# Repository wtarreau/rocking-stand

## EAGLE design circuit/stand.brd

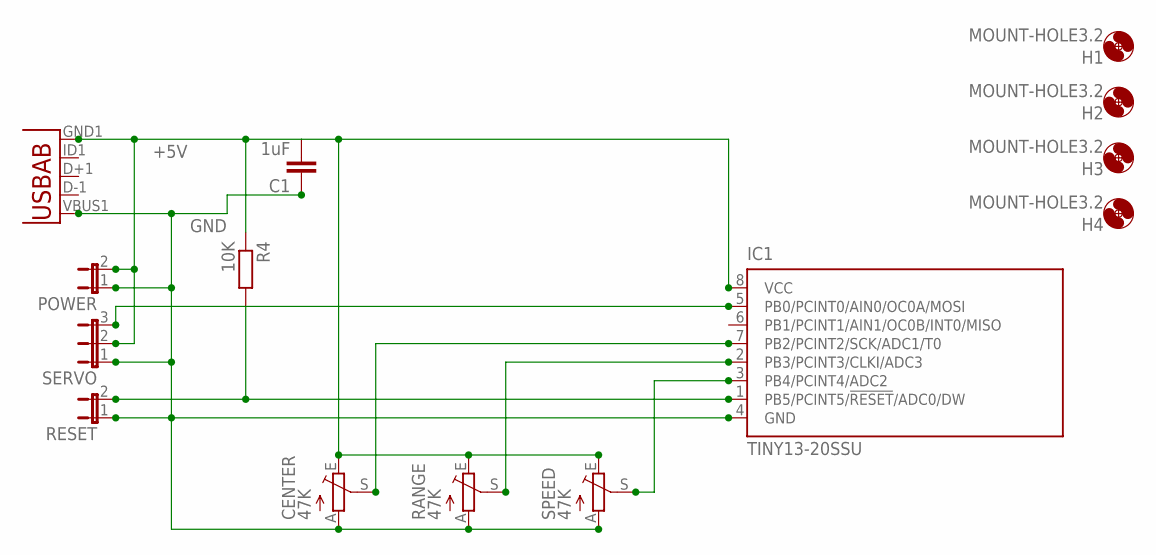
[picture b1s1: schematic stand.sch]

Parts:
C1: 1uF; C0805
CENTER: 47K; RJ6S
H1, H2, H3, H4: MOUNT-HOLE3.2; 3,2
IC1: TINY13-20SSU; 8S1
POWER: JP1E; JP1
R4: 10K; M0805
RANGE: 47K; RJ6S
RESET: JP1E; JP1
SERVO: JP2E; JP2
SPEED: 47K; RJ6S
U$1: USB""; USB-MICRO-SMD

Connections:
+5V: C1.2, CENTER.E, IC1.8 (VCC), POWER.2, R4.1, RANGE.E, SERVO.2, SPEED.E, U$1.GND1 (GND)
GND: C1.1, CENTER.A, IC1.4 (GND), POWER.1, RANGE.A, RESET.1, SERVO.1, SPEED.A, U$1.VBUS1 (VBUS)
unnamed: IC1.3 (PB4/PCINT4/ADC2), SPEED.S
unnamed: IC1.2 (PB3/PCINT3/CLKI/ADC3), RANGE.S
unnamed: IC1.1 (PB5/PCINT5/!RESET!/ADC0/DW), R4.2, RESET.2
unnamed: IC1.5 (PB0/PCINT0/AIN0/OC0A/MOSI), SERVO.3
unnamed: CENTER.S, IC1.7 (PB2/PCINT2/SCK/ADC1/T0)

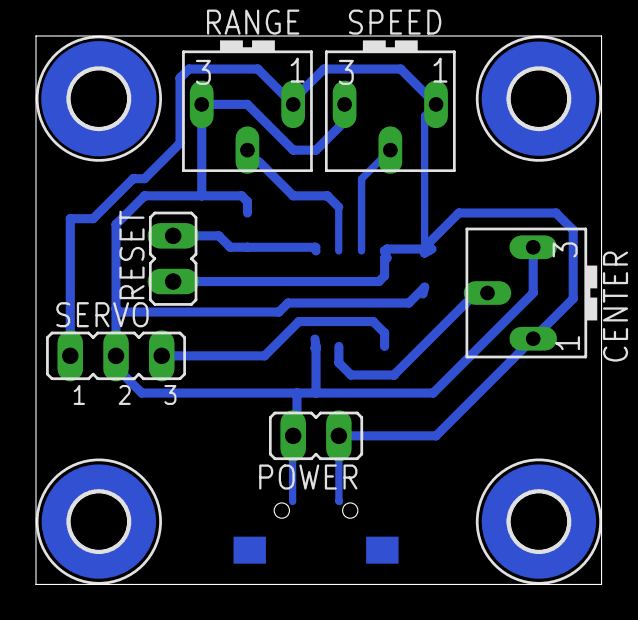
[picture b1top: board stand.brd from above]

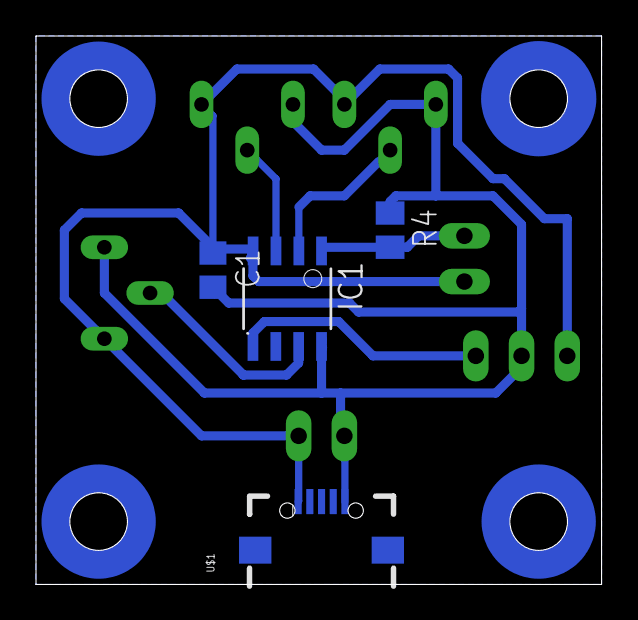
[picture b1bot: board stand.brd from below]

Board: 2 copper layers, 31.4 x 30.5 mm, 14 parts (4 on the bottom side), 7 nets.

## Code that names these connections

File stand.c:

/* stand.c - 2019/07/28 - Willy Tarreau - public domain
 *
 * This is a C AVR re-implementation of my previous rocking stand for PIC
 * that was written in 12F675 assembly. It implements a slow sine wave whose
 * amplitude, offset and frequency are controlled by 3 external potentiometers,
 * and converts it into a pulse length to drive a servo-motor. A sine wave was
 * found to be critical to avoid splashes when changing direction. The offset
 * is used to fix the center and to allow to repurpose old servos with broken
 * gears which can only operate on limited range.
 *
 * The code is written in Arduino style using setup() and loop() so that it is
 * easily ported to other environments. But it has no external dependency. It's
 * about 492 bytes on ATtiny13 and 506 on ATtiny85.
 */

/* Internal frequency, 9.6 MHz for Tiny13A, 8.0 MHz for 25/45/85 */
#ifndef F_CPU
#error "Must set F_CPU to the CPU's frequency in Hz"
#endif

#include <avr/io.h>
#include <stdint.h>

/* current angle in the highest 8 bits */
uint16_t angle = 0;

/* returns ((x*x) >> 7) + 128 using exclusively a 8*8=>16 bit signed
 * multiply. AVR: ~0x18 bytes + call to mulhi3().
 */
uint8_t sq8(int8_t x)
{
	x += 128;
	x = ((int16_t)x * x) >> 7;
	return ~x;
}

/* returns sin(angle*pi/128)*128, which is a sine centered around 0.
 * It works by approximating two paraboles. sin(x) follows x^2 and
 * 1-(x^2) very closely (6% error max) so these are sufficient.
 */
int8_t sin8(uint8_t angle)
{
	uint8_t ret = sq8(angle << 1);

	if (angle & 128)
		ret = ~ret;
	return ret + 128;
}

/* Convert microseconds to loops around an empty asm statement. Each loop was
 * measured to take 5 cycles on gcc 5.4 (vs 4 on 4.3)! This is limited to 64k
 * loops, or ~20ms at 8 MHz, 17ms at 9.6 MHz.
 */
static inline uint16_t us2loops(uint16_t us)
{
	return (uint32_t)us * (F_CPU / 100000) / 50 + 1;
}

/* Sleeps this number of microseconds. Limited ~32ms at 8 MHz, 27ms
 * at 9.6 MHz. May overflow on 8 MHz CPUs above 8 milliseconds at once.
 */
static inline void delay_us(uint16_t us)
{
	us = us2loops(us);
	while (--us)
		asm volatile("");
}

/* send a positive pulse of <width> microseconds on port B<port> */
static inline void send_pulse(uint8_t port, uint16_t width)
{
	width = us2loops(width);
	PORTB |= _BV(port);
	while (--width)
		asm volatile("");
	PORTB &= ~_BV(port);
}

/* configure the ADC channel between 0 to 3 */
static inline void set_adc_channel(const uint8_t ch)
{
	switch (ch) {
	case 0:	ADMUX = (ADMUX & ~(_BV(MUX1) | _BV(MUX0))) | (0         | 0);
		break;
	case 1:	ADMUX = (ADMUX & ~(_BV(MUX1) | _BV(MUX0))) | (0         | _BV(MUX0));
		break;
	case 2:	ADMUX = (ADMUX & ~(_BV(MUX1) | _BV(MUX0))) | (_BV(MUX1) | 0);
		break;
	case 3:	ADMUX = (ADMUX & ~(_BV(MUX1) | _BV(MUX0))) | (_BV(MUX1) | _BV(MUX0));
		break;
	}
}

/* starts the ADC conversion */
static inline void start_adc(void)
{
	ADCSRA |= _BV(ADSC);
}

/* reads the highest 8 bits of the ADC once ready */
static inline uint8_t read_adch(void)
{
	while (ADCSRA & _BV(ADSC))
		;
	/* result left aligned (8-bit in ADCH) => ADLAR = 1 */
	ADMUX |= _BV(ADLAR);
	return ADCH;
}

/* reads the 10 bits of the ADC once ready */
static inline uint16_t read_adc(void)
{
	while (ADCSRA & _BV(ADSC))
		;
	/* result right aligned (10-bit in ADCH:ADCL) => ADLAR = 0 */
	ADMUX &= ~_BV(ADLAR);
	return ADCL + ((uint16_t)ADCH << 8);
}

/* The loop is pretty simple. It runs for roughly 20 ms, measures the 3
 * potentiometers, computes the pulse length and position and sends it to
 * port PB0. Since the ADC conversion takes some time, we include it
 * in the pause delay. Thus we start a conversion on a port, wait 6 ms,
 * wait for the conversion to finish, start another one etc. This totals
 * 18 ms, to which we add roughly 1.5ms.
 */
void loop(void)
{
	uint16_t p1; // Potentiometer 1 : offset
	uint16_t p2; // Potentiometer 2 : speed
	uint8_t  p3; // Potentiometer 3 : amplitude
	uint16_t pw; // pulse_width

	p1 = 0; p2 = 0; p3 = 0;

	/* start conversion for ADC1, wait 6 ms and read it */
	set_adc_channel(1);
	start_adc();
	delay_us(6000);
	p1 = read_adc();

	/* start conversion for ADC2, wait 6 ms and read it */
	set_adc_channel(2);
	start_adc();
	delay_us(6000);
	p2 = read_adc();

	/* start conversion for ADC3, wait 6 ms and read it */
	set_adc_channel(3);
	start_adc();
	delay_us(6000);
	p3 = read_adch();

	/* note: ~18 ms elapsed here */

	/* the amplitude is 0..255. We multiply it by 4/256 before applying it
	 * to the signed sine (-128..127) so that we have a -510..508 range
	 * around 1500us. We then add the offset between -1024..+1022
	 */
	pw =	1500 + // center
		((int16_t)(p1 - 512) << 1) + // offset: -1024..+1022
		(((int16_t)sin8(angle >> 8) * p3) >> 6); // current angle

	/* we roughly perform this increment 50 times a second. This means that
	 * a complete cycle will be done ~3 times per second this way at the
	 * fastest speed.
	 */
	angle += (uint16_t)p2 << 2;
	send_pulse(PB0, pw);

	/* now we're around 18..22 ms */
}

void setup(void)
{
	/* PB#  pin  dir  role
	 * PB0   5   out  servo
	 * PB1   6    -   unused
	 * PB2   7    in  ADC1 - offset
	 * PB3   2    in  ADC3 - amplitude
	 * PB4   3    in  ADC2 - speed
	 * PB5   1    -   RESET
	 */

	/* set output pins */
	DDRB = _BV(DDB0);

	/* ADC sampling rate : clk/8 => ADPS{2,1,0} = 011 */
	/* ADEN=1 to enable ADC */
	ADCSRA = _BV(ADEN) | _BV(ADPS1) | _BV(ADPS0);

	/* ADC reference : Vcc => REFS0 = 0 */
	ADMUX = 0;
}

int main(void)
{
	setup();
#if TEST
	/* must produce exactly 1 KHz signal on PB0 */
	while (1) {
		delay_us(500);
		PORTB ^= _BV(PB0);
	}
#else
	while (1)
		loop();
#endif
}

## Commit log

2019-09-22 stand: first version
    This implements a rocking stand to etch PCBs. It is a C reimplementation
    of my earlier 12f675-based one, but with an AVR this time. 3 potentiometers
    are used :
    - p1 = center
    - p2 = speed
    - p3 = amplitude
2019-09-22 stand: increase range for the centering
    In order to be able to more easily reuse servos with broken gears, we
    need to cover a larger range for the center. This also requires to
    increase the possible amplitude around the 1500 us center, and in order
    to limit measurement noise, we'll retrieve the full 10-bit ADC values
    for the center and the speed instead of using only 8-bit shifted left,
    which is prone to noise. Now it is possible to make the servo oscillate
2019-09-22 stand: commit the experimental code, gnuplot functions and captures
    These files were used to recover the original function and to
    experiment with a few implementations to find the most optimal
    one in terms of code size. Let's not lose them a second time.
2019-09-22 firmware: commit the pre-compiled firmwares for attiny13 and attiny85
    This will help those without an AVR toolchain by allowing them to
    directly flash these files to the MCU. Both versions are very small
    and even compatible with a boot loader if desired.
2019-09-22 circuit: commit the schematic and board
    This is the latest version with 3 potentiometers to adjust :
    - speed
    - range
    - centering
    There's also a jumper to maintain the board in reset state. It can be
    more convenient than unplugging the power supply sometimes.
